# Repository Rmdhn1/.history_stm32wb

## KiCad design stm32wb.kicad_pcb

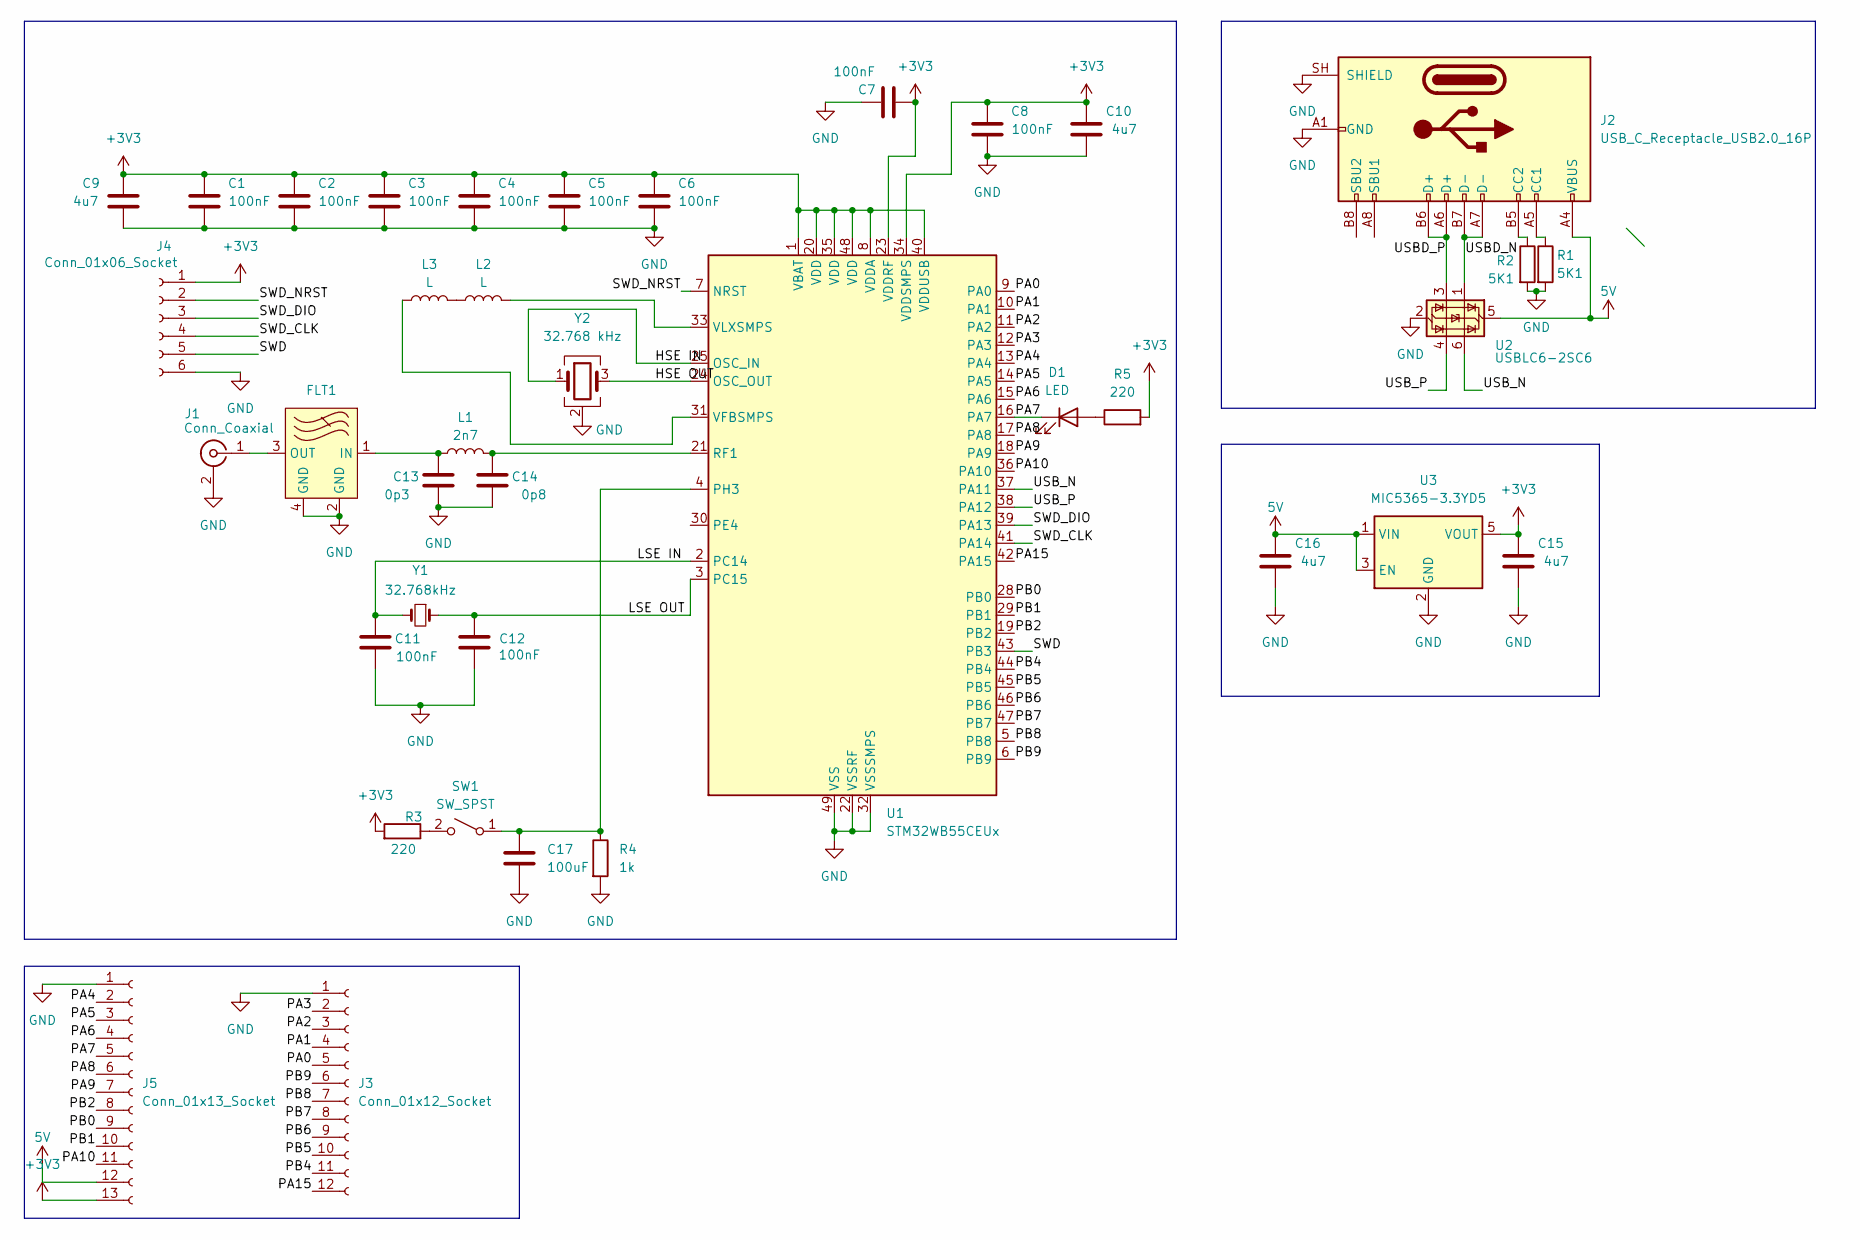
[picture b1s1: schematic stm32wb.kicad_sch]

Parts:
C1, C2, C3, C4, C5, C6, C7, C8, C11, C12: 100nF; C_0603_1608Metric_Polar
C9, C10, C15, C16: 4u7; C_0603_1608Metric_Polar
C13: 0p3; C_0603_1608Metric_Polar
C14: 0p8; C_0603_1608Metric_Polar
C17: 100uF; C_0603_1608Metric_Polar
D1: LED; LED_0805_2012Metric
FLT1: DLF-4_1P6X0P8
J1: Conn_Coaxial; BNC_Amphenol_B6252HB-NPP3G-50_Horizontal
J2: USB_C_Receptacle_USB2.0_16P; USB_C_Receptacle_HCTL_HC-TYPE-C-16P-01A
J3: Conn_01x12_Socket; PinHeader_1x12_P1.27mm_Vertical
J4: Conn_01x06_Socket; PinHeader_2x03_P1.27mm_Horizontal
J5: Conn_01x13_Socket; PinHeader_1x13_P1.27mm_Vertical
L1: 2n7; L_1206_3216Metric_Pad1.22x1.90mm_HandSolder
L2, L3: L; L_1206_3216Metric_Pad1.22x1.90mm_HandSolder
R1, R2: 5K1; R_0603_1608Metric
R3, R5: 220; R_0603_1608Metric
R4: 1k; R_0603_1608Metric
SW1: SW_SPST; SW_Push_1P1T_NO_CK_KSC6xxJ
U1: STM32WB55CEUx; QFN-48-1EP_7x7mm_P0.5mm_EP5.6x5.6mm
U2: USBLC6-2SC6; SOT-23-6
U3: MIC5365-3.3YD5; TSOT-23-5
Y1: 32.768kHz; Crystal_SMD_MicroCrystal_CC7V-T1A-2Pin_3.2x1.5mm
Y2: 32.768 kHz; Oscillator_SMD_ECS_2520MV-xxx-xx-4Pin_2.5x2.0mm

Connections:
5V: C16.2, J2.A4 (VBUS), J2.A9 (VBUS), J2.B4 (VBUS), J2.B9 (VBUS), J5.12, U2.5 (VBUS), U3.1 (VIN), U3.3 (EN)
+3V3: C1.2, C2.2, C3.2, C4.2, C5.2, C6.2, C7.1, C8.2, C9.2, C10.2, C15.2, J4.1, J5.13, R3.2, R5.2, U1.1 (VBAT), U1.8 (VDDA), U1.20 (VDD), U1.23 (VDDRF), U1.34 (VDDSMPS), U1.35 (VDD), U1.40 (VDDUSB), U1.48 (VDD), U3.5 (VOUT)
/HSE IN: U1.25 (OSC_IN), Y2.1
/HSE OUT: U1.24 (OSC_OUT), Y2.3
/LSE IN: C11.1, U1.2 (PC14), Y1.2
/LSE OUT: C12.1, U1.3 (PC15), Y1.1
/PA0: J3.5, U1.9 (PA0)
/PA1: J3.4, U1.10 (PA1)
/PA2: J3.3, U1.11 (PA2)
/PA3: J3.2, U1.12 (PA3)
/PA4: J5.2, U1.13 (PA4)
/PA5: J5.3, U1.14 (PA5)
/PA6: J5.4, U1.15 (PA6)
/PA7: D1.1 (K), J5.5, U1.16 (PA7)
/PA8: J5.6, U1.17 (PA8)
/PA9: J5.7, U1.18 (PA9)
/PA10: J5.11, U1.36 (PA10)
/PA15: J3.12, U1.42 (PA15)
/PB0: J5.9, U1.28 (PB0)
/PB1: J5.10, U1.29 (PB1)
/PB2: J5.8, U1.19 (PB2)
/PB4: J3.11, U1.44 (PB4)
/PB5: J3.10, U1.45 (PB5)
/PB6: J3.9, U1.46 (PB6)
/PB7: J3.8, U1.47 (PB7)
/PB8: J3.7, U1.5 (PB8)
/PB9: J3.6, U1.6 (PB9)
/SWD: J4.5, U1.43 (PB3)
/SWD_CLK: J4.4, U1.41 (PA14)
/SWD_DIO: J4.3, U1.39 (PA13)
/SWD_NRST: J4.2, U1.7 (NRST)
/USBD_N: J2.A7 (D-), J2.B7 (D-), U2.1 (I/O1)
/USBD_P: J2.A6 (D+), J2.B6 (D+), U2.3 (I/O2)
/USB_N: U1.37 (PA11), U2.6 (I/O1)
/USB_P: U1.38 (PA12), U2.4 (I/O2)
GND: C1.1, C2.1, C3.1, C4.1, C5.1, C6.1, C7.2, C8.1, C9.1, C10.1, C11.2, C12.2, C13.2, C14.2, C15.1, C16.1, C17.2, FLT1.2 (GND), FLT1.4 (GND), J1.2 (Ext), J2.A1 (GND), J2.A12 (GND), J2.B1 (GND), J2.B12 (GND), J2.SH (SHIELD), J3.1, J4.6, J5.1, R1.2, R2.2, R4.2, U1.22 (VSSRF), U1.32 (VSSSMPS), U1.49 (VSS), U2.2 (GND), U3.2 (GND), Y2.2 (G), Y2.4 (G)
unnamed: D1.2 (A), R5.1
unnamed: C13.1, FLT1.1 (IN), L1.1
unnamed: FLT1.3 (OUT), J1.1 (In)
unnamed: J2.A5 (CC1), R1.1
unnamed: J2.B5 (CC2), R2.1
unnamed: L2.1, L3.2
unnamed: C17.1, R4.1, SW1.1 (A), U1.4 (PH3)
unnamed: R3.1, SW1.2 (B)
unnamed: C14.1, L1.2, U1.21 (RF1)
unnamed: L3.1, U1.31 (VFBSMPS)
unnamed: L2.2, U1.33 (VLXSMPS)

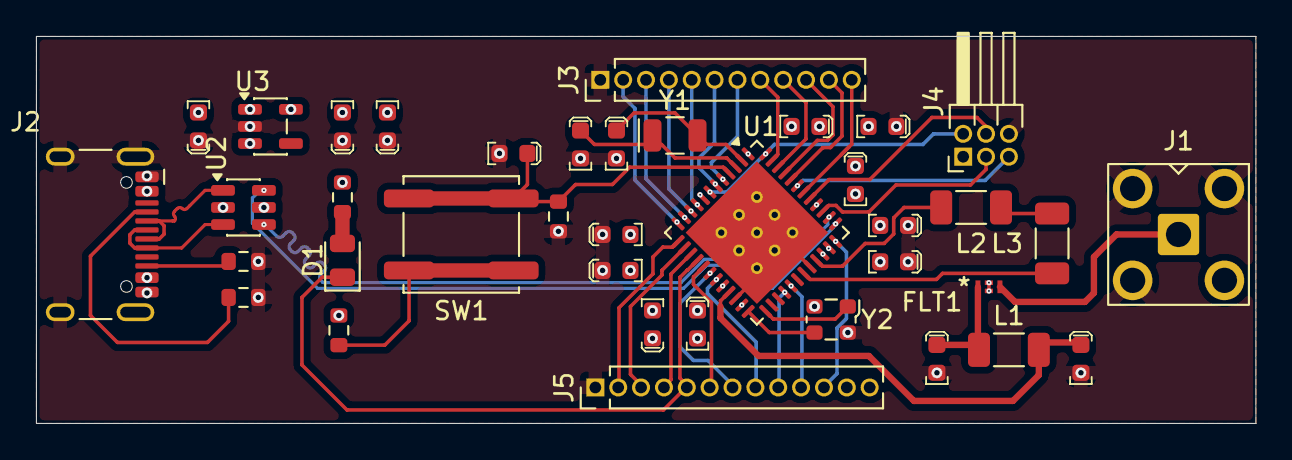
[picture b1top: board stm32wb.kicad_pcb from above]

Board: 4 copper layers, 67.8 x 21.5 mm, 38 parts (0 on the bottom side), 47 nets.
